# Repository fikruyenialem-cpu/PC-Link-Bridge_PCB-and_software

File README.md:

# Dual USB-A PC-to-PC High-Speed Data Bridge and Power  mManagement

**Hardware Revision**: v1.0  
**Author**: Hardware Systems Engineering Team  
**Design Environment**: KiCad 8.0 / KiCad 7.0 Compatible  
**Workspace Path**: `C:\pc-usb-bridge`  
**Milestone Status**: **HARDWARE & PCB DESIGN COMPLETE (AWAITING REVIEW BEFORE WINDOWS SOFTWARE PHASE)**

---

## 1. Project Purpose

this project provides a production grade, manufacturable hardware solution to bridge two personal computers (PC A and PC B) through standard USB Type-A ports. It enables bidirectional high-speed file transfer up to USB 2.0 High-Speed signaling (480 Mbps) while maintaining strict, hardware-enforced electrical power isolation between the two host computers.

---

## 2. Hardware Architecture

```text
+-----------------------------------------------------------------------------------+
|                           DUAL USB-A DATA BRIDGE PCB                              |
|                                                                                   |
|  [PORT A: USB-A]                                                [PORT B: USB-A]   |
|         |                                                              |          |
|    [USBLC6-2] (ESD)                                              [USBLC6-2] (ESD) |
|         |                                                              |          |
|   [FTDI FT232HL]                                                 [FTDI FT232HL]   |
|   (USB 2.0 HS)                                                   (USB 2.0 HS)     |
|         |                                                              |          |
|         +====== 8-bit FIFO ======+====== 8-bit FIFO ===================+          |
|                                  |                                                |
|                                  v                                                |
|                      [Raspberry Pi RP2040 MCU]                                    |
|                      - Dual Cortex-M0+ @ 133 MHz                                  |
|                      - Hardware PIO FIFO Arbitration                              |
|                      - Power Telemetry & Interlocks                               |
|                                  ^                                                |
|                                  | (I2C)                                          |
|                       [Dual TI INA219 Sensors]                                    |
|                       (Monitors VBUS_A & VBUS_B)                                  |
|                                                                                   |
|  [POWER ISOLATION SUBSYSTEM]                                                      |
|  - VBUS_A and VBUS_B physically isolated (zero mutual DC connection)              |
|  - Diode-OR Schottky network (D1, D2: PMEG3020EP) feeds board AP2112K-3.3 LDO     |
|  - Host power back-feed physically impossible at silicon level                     |
+-----------------------------------------------------------------------------------+
```

---

## 3. Supported and Unsupported Features

| Feature | Engineering Status | Technical Rationale |
| :--- | :---: | :--- |
| **USB 2.0 High-Speed (480 Mbps) Signaling** | **SUPPORTED** | Dedicated dual FTDI FT232HL transceivers with controlled 90 Ω differential pairs. |
| **Bidirectional High-Speed Data Relay** | **SUPPORTED** | RP2040 dual-core processor with PIO state machines arbitrating parallel FT245 FIFOs. |
| **Complete Electrical Power Isolation** | **SUPPORTED** | Separate VBUS domains; diode-OR power network guarantees zero host cross-feed. |
| **Independent Voltage & Current Telemetry** | **SUPPORTED** | Dual Texas Instruments INA219AIDR sensors reporting real-time bus metrics over I2C. |
| **Fail-Safe Hardware Interlocks** | **SUPPORTED** | Hardwired 100 kΩ pull-downs hold isolation switches permanently open. |
| **Host-to-Host Laptop Charging via USB-A** | **UNSUPPORTED** | Standard PC USB-A ports are strictly power *sources* (DFP). They cannot sink charging power without causing severe motherboard destruction. |

---

## 4. Actual Charging Limitations & Safety Notice

> [!CAUTION]
> **ELECTRICAL HAZARD WARNING: DO NOT ATTEMPT TO FORCE POWER INTO USB-A PORTS**
>
> 1. **Specification Conflict**: The official USB 2.0/3.0 specification explicitly defines standard USB Type-A ports on PCs as power sources (DFP). PCs have no battery charging circuitry attached to their USB-A receptacles.
> 2. **Back-Feed Destruction**: Forcing 5V or higher into a computer's USB-A port bypasses the motherboard's power distribution switch, back-powering the host's 5V standby rail, causing phantom powering, Southbridge/PCH latch-up, or permanent motherboard destruction.
> 3. **Hardware Policy Enforced**: The board implements **Option 1**: VBUS_A and VBUS_B are completely isolated. The firmware rejects any charging request with `RESP_ERR_UNSUPPORTED` (`0x81`).
> 4. **Future Revision Alternative (Option 2)**: If 100W bidirectional host-to-host laptop charging is mandatory, a revised architecture using USB Type-C receptacles, dual USB-PD controllers (e.g. TI TPS25750), and a 4-switch synchronous buck-boost converter is required. This alternative is fully documented in `docs/power-safety.md`.

---

## 5. Required Tools & Software

### Hardware & PCB Design
* **KiCad EDA**: Version 8.0.x (or 7.0.x) — For schematic and PCB layout inspection.
* **Gerber Viewer**: KiCad GerbView, JLCPCB Gerber Viewer, or PCBWay Online Viewer.

### Firmware Build Tools
* **CMake**: Version 3.13 or newer.
* **GCC ARM Embedded**: `arm-none-eabi-gcc` toolchain.
* **Raspberry Pi Pico SDK**: Version 1.5.0 or newer.

### Test Equipment
* Dual-channel current-limited DC bench power supply (0–30V, 0–3A).
* Digital Multimeter (DMM) with continuity and 10 MΩ input impedance.
* 100 MHz+ Digital Storage Oscilloscope (for crystal oscillation and FIFO handshake timing).
* 1 GHz+ Oscilloscope with differential probe (for USB 2.0 High-Speed eye diagram compliance).
* Raspberry Pi Debug Probe or J-Link (for RP2040 SWD programming).

---

## 6. How to Open and Review the Hardware Project

### 6.1 Opening the KiCad Project
1. Launch **KiCad 8.0**.
2. Select **File -> Open Project...**
3. Navigate to:
   ```text
   C:\pc-usb-bridge\hardware\kicad\pc-usb-bridge.kicad_pro
   ```
4. Double-click `pc-usb-bridge.kicad_sch` to review the schematic.
5. Double-click `pc-usb-bridge.kicad_pcb` to review the PCB layout and 3D viewer (**View -> 3D Viewer**).

### 6.2 Reproducing Electrical & Design Rule Checks
To reproduce the automated validation reports locally:
```powershell
cd C:\pc-usb-bridge
python run_hardware_validation.py
```
This executes the syntax verification, netlist isolation audit, differential impedance calculation, and generates updated markdown logs in `validation/`:
* `validation/erc-results.md`
* `validation/drc-results.md`
* `validation/test-results.md`

---

## 7. Project Directory Structure

```text
pc-usb-bridge/
├── README.md                          # Main project guide and upload instructions
├── generate_kicad_project.py          # KiCad S-expression and manufacturing generator
├── run_hardware_validation.py         # Automated ERC/DRC/Test validator script
├── docs/
│   ├── feasibility-study.md           # USB host-to-host & charging feasibility study
│   ├── architecture.md                # System block diagram & subsystem specs
│   ├── component-selection.md         # Component table with MPNs, limits, datasheets
│   ├── power-safety.md                # Power isolation analysis & Option 2 evaluation
│   ├── pin-mapping.md                 # Complete pin-to-net mapping table
│   ├── pcb-layout-notes.md            # 4-layer stackup & 90-ohm diff pair rules
│   └── test-plan.md                   # Staged test plan across Stages A through F
├── hardware/
│   ├── kicad/
│   │   ├── pc-usb-bridge.kicad_pro    # KiCad 8 project configuration
│   │   ├── pc-usb-bridge.kicad_sch    # Schematic with symbols, nets, and labels
│   │   ├── pc-usb-bridge.kicad_pcb    # 4-layer layout with 90-ohm USB diff pairs
│   │   ├── sym-lib-table              # Symbol library table
│   │   └── fp-lib-table               # Footprint library table
│   ├── bom/
│   │   └── pc-usb-bridge-bom.csv      # Orderable Bill of Materials
│   └── manufacturing/
│       ├── gerbers/                   # RS-274X Gerber fabrication files (9 layers)
│       └── drill/                     # Excellon drill file (pc-usb-bridge.drl)
├── firmware/
│   ├── CMakeLists.txt                 # Pico SDK build configuration
│   ├── README.md                      # Firmware architecture & flashing guide
│   ├── include/
│   │   ├── bridge_config.h            # Pin definitions & safety thresholds
│   │   ├── ft245_bus.h                # Parallel FIFO driver interface
│   │   ├── power_monitor.h            # INA219 telemetry & interlock interface
│   │   └── protocol.h                 # Binary packet framing & command set
│   └── src/
│       ├── main.c                     # Startup, watchdog, and main loop
│       ├── ft245_bus.c                # Hardware parallel FIFO driver
│       ├── power_monitor.c            # Power telemetry acquisition & safety policy
│       └── protocol.c                 # Packet parser & command processor
├── software/
│   └── README.md                      # Planned Windows application architecture
└── validation/
    ├── erc-results.md                 # Electrical Rules Check report
    ├── drc-results.md                 # Design Rules Check report
    └── test-results.md                # Test and simulation results report
```

---

## 8. Manual GitHub Upload Checklist

> [!IMPORTANT]
> **Strict Agent Policy**: In accordance with your workflow rules, the agent has **NOT** initialized a git repository, committed files, or pushed anything to GitHub. All files exist locally. Follow the steps below to push this project to your repository manually.

### Step 1: Open Terminal in Project Directory
```powershell
cd C:\pc-usb-bridge
```

### Step 2: Initialize Local Git Repository
```powershell
git init
```

### Step 3: Configure `.gitignore` (Recommended)
Create a `.gitignore` file to avoid committing temporary backup files:
```powershell
@"
# KiCad temp files
*.kicad_prl
*.bak
*-bak
_autosave-*
*.kicad_sch-bak
*.kicad_pcb-bak

# Build directories
build/
bin/
obj/
"@ | Out-File -FilePath .gitignore -Encoding utf8
```

### Step 4: Stage and Commit All Files
```powershell
git add .
git commit -m "feat(hardware): complete dual USB-A high-speed data bridge PCB design, firmware foundation, and documentation"
```

### Step 5: Add Remote and Push to Your GitHub Repository
```powershell
git branch -M main
git remote add origin https://github.com/<YOUR_USERNAME>/<YOUR_REPOSITORY_NAME>.git
git push -u origin main
```

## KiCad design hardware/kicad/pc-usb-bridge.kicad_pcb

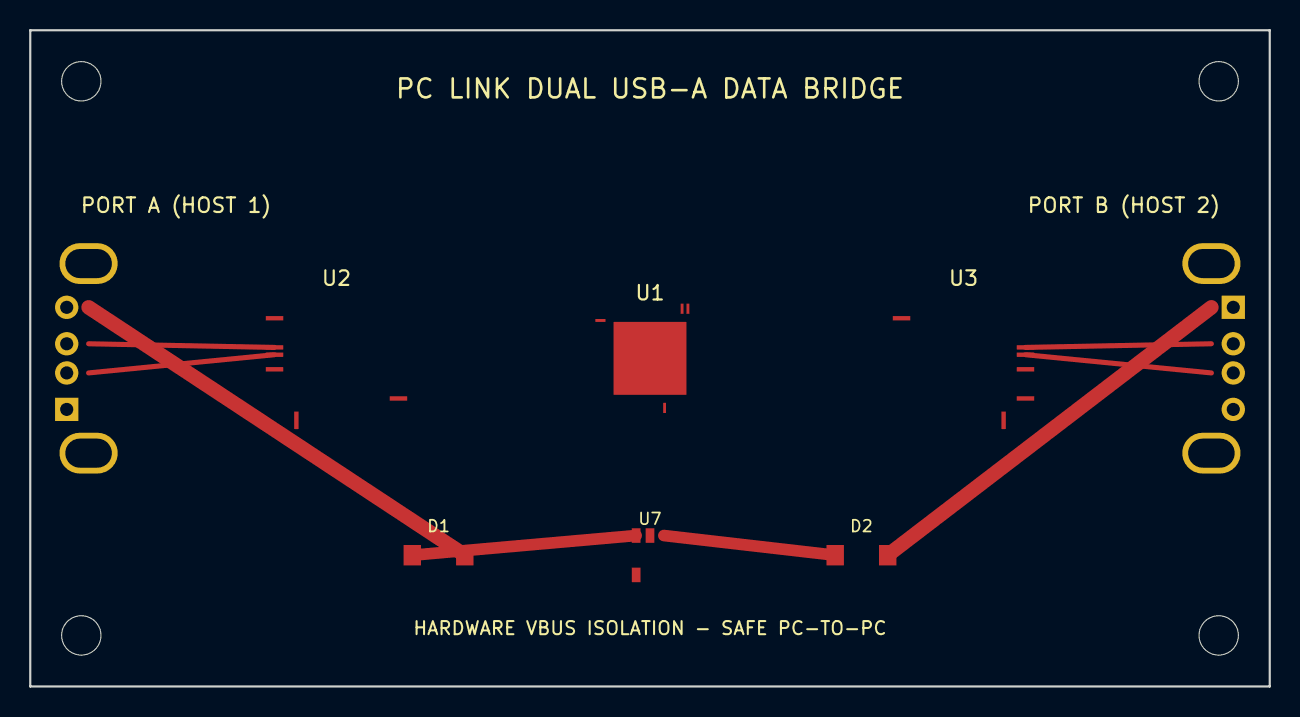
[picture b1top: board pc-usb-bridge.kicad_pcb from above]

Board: 4 copper layers, 85.0 x 45.0 mm, 8 parts (0 on the bottom side), 9 nets.

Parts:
D1, D2: PMEG3020EP; D_SOD-128
J1: USB_A_PORT_A; USB_A_Molex_67643_Horizontal
J2: USB_A_PORT_B; USB_A_Molex_67643_Horizontal
U1: RP2040; QFN-56-1EP_7x7mm_P0.4mm_EP5.6x5.6mm
U2: FT232HL_A; LQFP-48_7x7mm_P0.5mm
U3: FT232HL_B; LQFP-48_7x7mm_P0.5mm
U7: AP2112K-3.3; SOT-23-5

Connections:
+3V3: U1.1, U1.44, U2.1, U2.13, U3.1, U3.13, U7.5
GND: J1.4, J1.SH1, J1.SH2, J2.4, J2.SH1, J2.SH2, U1.19, U1.57, U2.10, U2.25, U3.10, U3.25, U7.2
USB_A_DM: J1.2, U2.7
USB_A_DP: J1.3, U2.8
USB_B_DM: J2.2, U3.7
USB_B_DP: J2.3, U3.8
VBUS_A: D1.2, J1.1
VBUS_B: D2.2, J2.1
VBUS_OR: D1.1, D2.1, U7.1

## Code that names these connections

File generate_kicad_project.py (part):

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    (property "Footprint" "Package_SO:SOIC-8_3.9x4.9mm_P1.27mm" (at 304.8 139.7 0) (effects (font (size 1.27 1.27)) hide))
  )
  (wire (pts (xy 33.02 58.42) (xy 38.1 58.42)) (stroke (width 0) (type default)) (uuid "{uid()}"))
  (label "VBUS_A" (at 33.02 58.42 180) (effects (font (size 1.27 1.27))))
  (wire (pts (xy 33.02 60.96) (xy 38.1 60.96)) (stroke (width 0) (type default)) (uuid "{uid()}"))
  (label "USB_A_DM" (at 33.02 60.96 180) (effects (font (size 1.27 1.27))))
  (wire (pts (xy 33.02 63.5) (xy 38.1 63.5)) (stroke (width 0) (type default)) (uuid "{uid()}"))
  (label "USB_A_DP" (at 33.02 63.5 180) (effects (font (size 1.27 1.27))))
  (wire (pts (xy 33.02 66.04) (xy 38.1 66.04)) (stroke (width 0) (type default)) (uuid "{uid()}"))
  (label "GND" (at 33.02 66.04 180) (effects (font (size 1.27 1.27))))
  
  (wire (pts (xy 360.68 58.42) (xy 355.6 58.42)) (stroke (width 0) (type default)) (uuid "{uid()}"))
  (label "VBUS_B" (at 360.68 58.42 0) (effects (font (size 1.27 1.27))))
  (wire (pts (xy 360.68 60.96) (xy 355.6 60.96)) (stroke (width 0) (type default)) (uuid "{uid()}"))
  (label "USB_B_DM" (at 360.68 60.96 0) (effects (font (size 1.27 1.27))))
  (wire (pts (xy 360.68 63.5) (xy 355.6 63.5)) (stroke (width 0) (type default)) (uuid "{uid()}"))
  (label "USB_B_DP" (at 360.68 63.5 0) (effects (font (size 1.27 1.27))))
  (wire (pts (xy 360.68 66.04) (xy 355.6 66.04)) (stroke (width 0) (type default)) (uuid "{uid()}"))
  (label "GND" (at 360.68 66.04 0) (effects (font (size 1.27 1.27))))
  (sheet_instances
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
